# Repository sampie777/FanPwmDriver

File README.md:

# FanPwmDriver PCB

### Schematic

### Board

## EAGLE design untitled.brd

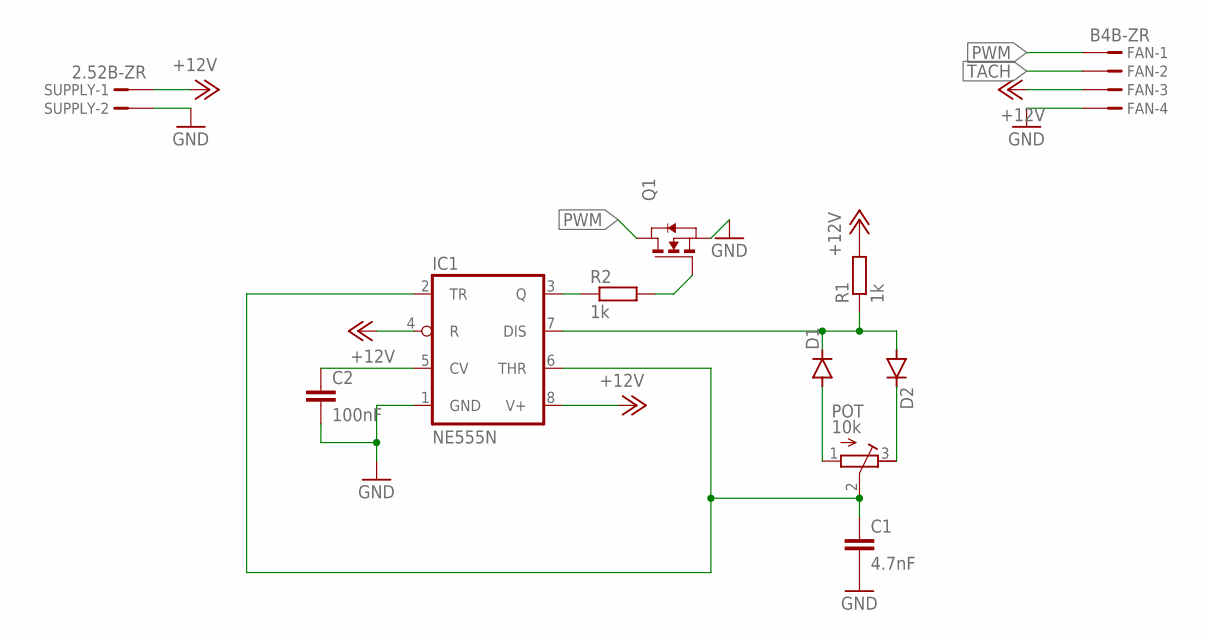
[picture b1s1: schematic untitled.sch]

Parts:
C1: 4.7nF; C050-030X075
C2: 100nF; C025-025X050
D1, D2: CGRM4001-G; SOD-123_MINI-SMA
FAN: B4B-ZR
IC1: NE555N; DIL08
POT: 10k; RTRIM3296W
Q1: NMOSSOT23; SOT-23
R1, R2: 1k; R0603
SUPPLY: 2.52B-ZR; B2B-ZR2.5

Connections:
+12V: FAN.3, IC1.4 (R), IC1.8 (V+), R1.2, SUPPLY.1
CV: C2.1, IC1.5 (CV)
DIS: D1.C, D2.A, IC1.7 (DIS), R1.1
GND: C1.2, C2.2, FAN.4, IC1.1 (GND), Q1.2 (S), SUPPLY.2
unnamed: Q1.3 (G), R2.2
unnamed: D1.A, POT.1 (A)
unnamed: D2.C, POT.3 (E)
PWM: FAN.1, Q1.1 (D)
Q: IC1.3 (Q), R2.1
TACH: FAN.2
TR: C1.1, IC1.2 (TR), IC1.6 (THR), POT.2 (S)

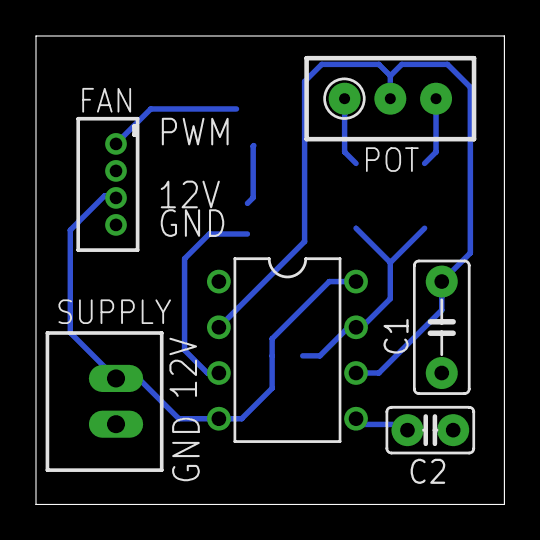
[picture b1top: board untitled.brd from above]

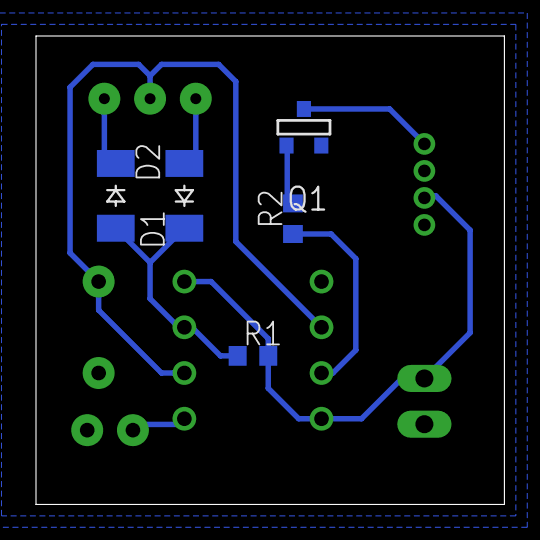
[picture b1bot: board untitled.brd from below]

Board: 2 copper layers, 26.0 x 26.0 mm, 11 parts (5 on the bottom side), 10 nets.

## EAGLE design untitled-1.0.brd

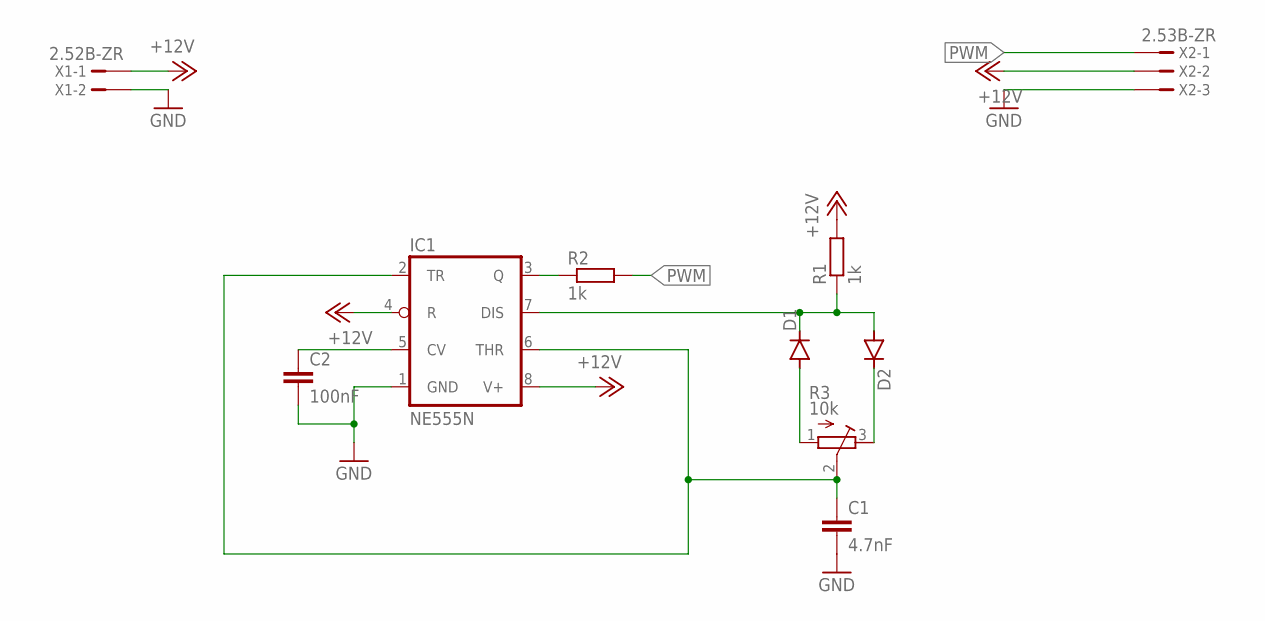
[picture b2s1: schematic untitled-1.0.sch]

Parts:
C1: 4.7nF; C050-030X075
C2: 100nF; C025-025X050
D1, D2: 1N40045; DO41-5
IC1: NE555N; DIL08
R1, R2: 1k; 0204/7
R3: 10k; RTRIM3296W
X1: 2.52B-ZR; B2B-ZR2.5
X2: 2.53B-ZR; B3B-ZR2.5

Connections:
+12V: IC1.4 (R), IC1.8 (V+), R1.2, X1.1, X2.2
CV: C2.1, IC1.5 (CV)
DIS: D1.C, D2.A, IC1.7 (DIS), R1.1
GND: C1.2, C2.2, IC1.1 (GND), X1.2, X2.3
unnamed: D1.A, R3.1 (A)
unnamed: D2.C, R3.3 (E)
PWM: R2.2, X2.1
Q: IC1.3 (Q), R2.1
TR: C1.1, IC1.2 (TR), IC1.6 (THR), R3.2 (S)

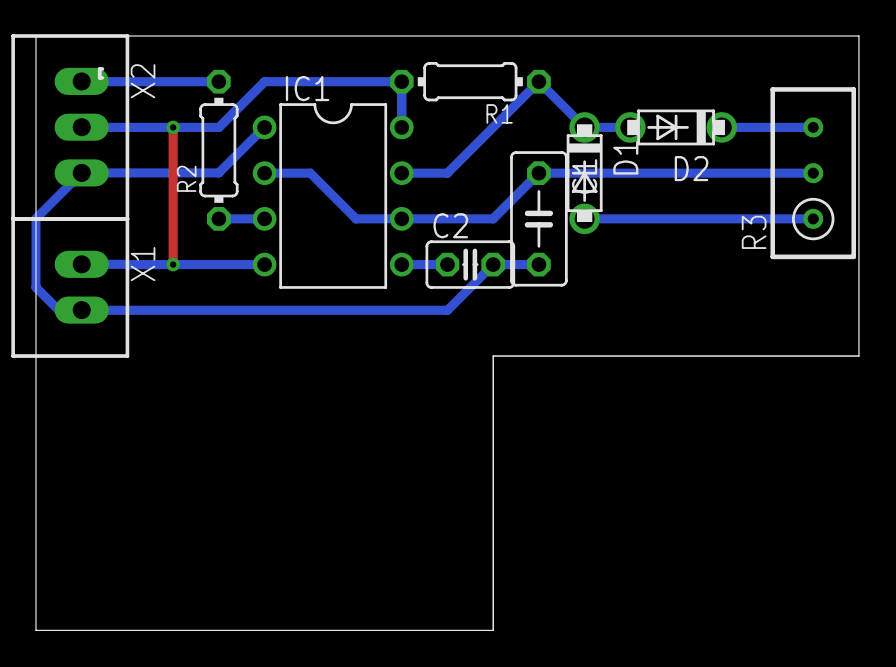
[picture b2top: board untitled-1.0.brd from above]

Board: 2 copper layers, 45.7 x 33.0 mm, 10 parts (0 on the bottom side), 9 nets.
